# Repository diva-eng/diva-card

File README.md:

# Diva Card

Raspberry RP2040 based development board/card with builtin LED matrix

## Specs
* RP2040 Dual ARM Cortex-M0+ @ 133MHz
* Microchip ATECC608A crypto processor
* 8*5 WS2812C-2020 RGB LED matrix
* USB-C connector at USB 2.0 speed
* 1 user Button
* 1 user LED
* 13 user IO
* SWD tag connector
 * Edge connector for IO/Power

## Firmware

See the example firmware and build instructions in `fw/README.md`.

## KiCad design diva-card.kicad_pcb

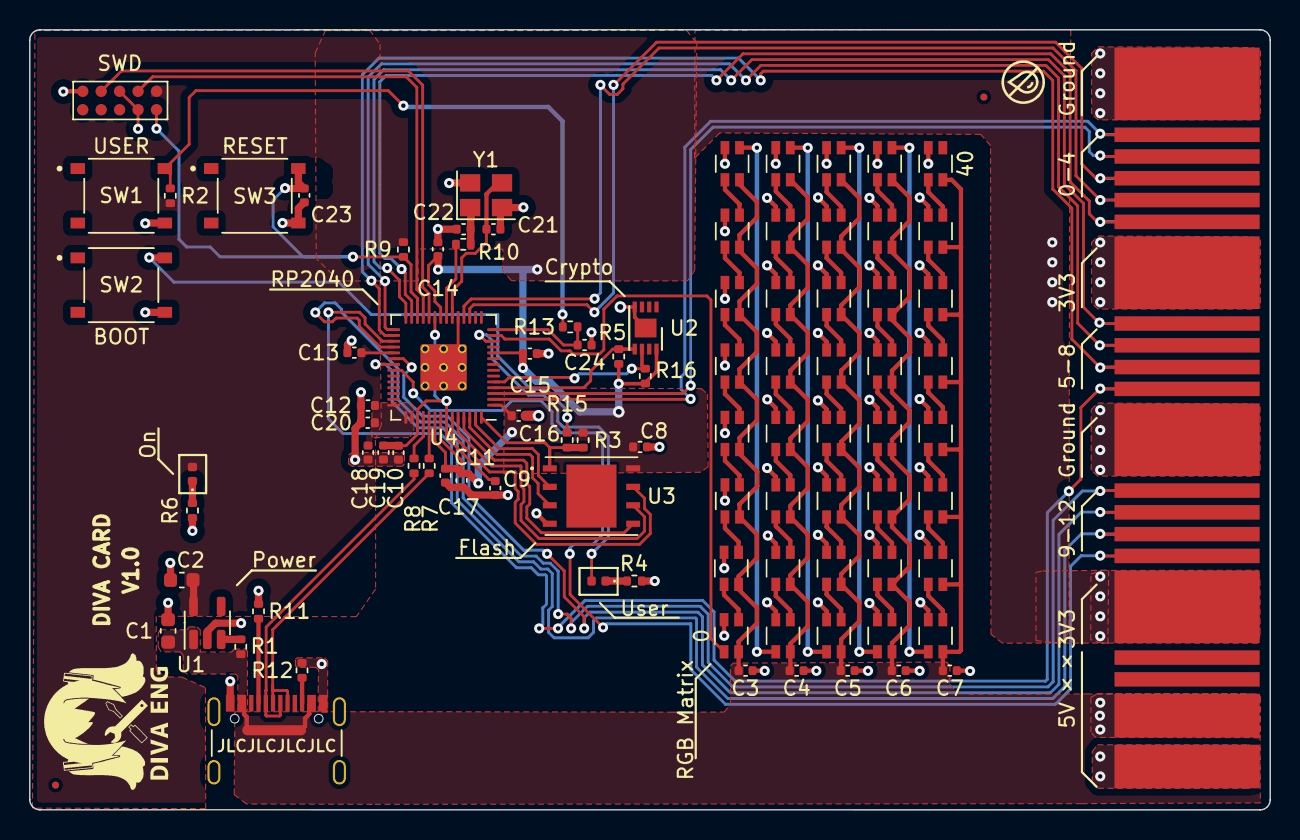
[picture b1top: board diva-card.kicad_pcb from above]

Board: 2 copper layers, 85.4 x 53.7 mm, 94 parts (0 on the bottom side), 84 nets.

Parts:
C1, C2: 10u; C_0603_1608Metric
C3, C4, C5, C6, C7, C8, C9, C10, C11, C12, C13, C14, C15, C16, C17, C18: 100n; C_0402_1005Metric
C19, C20, C23, C24: 1u; C_0402_1005Metric
C21, C22: 33p; C_0402_1005Metric
D1: EMERALD; LED_0402_1005Metric
D2: WHITE; LED_0402_1005Metric
FID1, FID2: Fiducial; Fiducial_0.5mm_Mask1mm
J1: Conn_02x05_Odd_Even; Tag-Connect_TC2050-IDC-NL_2x05_P1.27mm_Vertical
J2: USB_C_Receptacle_USB2.0; USB_C_Receptacle_Palconn_UTC16-G
J3: Conn_02x21_Odd_Even; PICO_CARD_EDGE_21
L1, L2, L3, L4, L5, L6, L7, L8, L9, L10, L11, L12, L13, L14, L15, L16, L17, L18, L19, L20, L21, L22, L23, L24, L25, L26, L27, L28, L29, L30, L31, L32, L33, L34, L35, L36, L37, L38, L39, L40: WS2812C; WS2812C-2020
R1, R2, R3, R13: 10k; R_0402_1005Metric
R4, R6: 1k5; R_0402_1005Metric
R5, R16: 4.7k; R_0402_1005Metric
R7, R8: 27; R_0402_1005Metric
R9: 10K; R_0402_1005Metric
R10: 100; R_0402_1005Metric
R11, R12: 5k1; R_0402_1005Metric
R15: 1K; R_0402_1005Metric
SW1: USER; SW_TS-1187A-B-A-B
SW2: BOOTSEL; SW_TS-1187A-B-A-B
SW3: RESET; SW_TS-1187A-B-A-B
U1: AP2112K-3.3; SOT-23-5
U2: ATECC608A-MAHDA; DFN-8-1EP_3x2mm_P0.5mm_EP1.3x1.5mm
U3: W25Q128XXX; W25Q128JVPIQ TR
U4: RP2040; RP2040-QFN-56
Y1: X322512MSB4SI; Crystal_SMD_3225-4Pin_3.2x2.5mm

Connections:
+1V1: C9.1, C10.1, C19.1, U4.23 (DVDD), U4.45 (VREG_VOUT), U4.50 (DVDD)
+3V3: C2.1, C8.1, C11.1, C12.1, C13.1, C14.1, C15.1, C16.1, C17.1, C18.1, C20.1, D2.2 (A), J1.1, J3.13, J3.14, J3.33, J3.34, R2.1, R3.1, R5.1, R9.1, R16.1, U1.5 (VOUT), U2.8 (VCC), U3.8 (VCC), U4.1 (IOVDD), U4.10 (IOVDD), U4.22 (IOVDD), U4.33 (IOVDD), U4.42 (IOVDD), U4.43 (ADC_AVDD), U4.44 (VREG_IN), U4.48 (USB_VDD), U4.49 (IOVDD)
+5V: C1.1, C3.1, C4.1, C5.1, C6.1, C7.1, J2.A4 (VBUS), J2.A9 (VBUS), J2.B4 (VBUS), J2.B9 (VBUS), J3.39, J3.40, L1.4 (VDD), L2.4 (VDD), L3.4 (VDD), L4.4 (VDD), L5.4 (VDD), L6.4 (VDD), L7.4 (VDD), L8.4 (VDD), L9.4 (VDD), L10.4 (VDD), L11.4 (VDD), L12.4 (VDD), L13.4 (VDD), L14.4 (VDD), L15.4 (VDD), L16.4 (VDD), L17.4 (VDD), L18.4 (VDD), L19.4 (VDD), L20.4 (VDD), L21.4 (VDD), L22.4 (VDD), L23.4 (VDD), L24.4 (VDD), L25.4 (VDD), L26.4 (VDD), L27.4 (VDD), L28.4 (VDD), L29.4 (VDD), L30.4 (VDD), L31.4 (VDD), L32.4 (VDD), L33.4 (VDD), L34.4 (VDD), L35.4 (VDD), L36.4 (VDD), L37.4 (VDD), L38.4 (VDD), L39.4 (VDD), L40.4 (VDD), R1.1, U1.1 (VIN)
/I2C0_SCL: R16.2, U2.6 (SCL), U4.5 (GPIO3)
/I2C0_SDA: R5.2, U2.5 (SDA), U4.4 (GPIO2)
/LED_DI: L1.3 (DI), U4.13 (GPIO10)
/USER_LED: D1.2 (A), U4.12 (GPIO9)
/connectors/SWDCLK: J1.4, U4.24 (SWCLK)
/connectors/SWDIO: J1.2, U4.25 (SWD)
/connectors/USB_D+: J2.A6 (D+), J2.B6 (D+), R7.2
/connectors/USB_D-: J2.A7 (D-), J2.B7 (D-), R8.2
/connectors/USER_IO_0: J3.3, J3.4, U4.2 (GPIO0)
/connectors/USER_IO_1: J3.5, J3.6, U4.3 (GPIO1)
/connectors/USER_IO_2: J3.7, J3.8, U4.17 (GPIO14)
/connectors/USER_IO_3: J3.9, J3.10, U4.18 (GPIO15)
/connectors/USER_IO_4: J3.11, J3.12, U4.27 (GPIO16)
/connectors/USER_IO_5: J3.15, J3.16, U4.28 (GPIO17)
/connectors/USER_IO_6: J3.17, J3.18, U4.29 (GPIO18)
/connectors/USER_IO_7: J3.19, J3.20, U4.30 (GPIO19)
/connectors/USER_IO_8: J3.21, J3.22, U4.31 (GPIO20)
/connectors/USER_IO_9: J3.25, J3.26, U4.32 (GPIO21)
/connectors/USER_IO_10: J3.27, J3.28, U4.34 (GPIO22)
/connectors/USER_IO_11: J3.29, J3.30, U4.35 (GPIO23)
/connectors/USER_IO_12: J3.31, J3.32, U4.36 (GPIO24)
/connectors/~RESET: C23.1, J1.10, R9.2, SW3.1, U4.26 (RUN)
/microcontroller/QSPI_SCLK: U3.6 (CLK), U4.52 (QSPI_SCLK)
/microcontroller/QSPI_SIO0: U3.5 (DI(IO0)), U4.53 (QSPI_SD0)
/microcontroller/QSPI_SIO1: U3.2 (DO(IO1)), U4.55 (QSPI_SD1)
/microcontroller/QSPI_SIO2: U3.3 (IO2), U4.54 (QSPI_SD2)
/microcontroller/QSPI_SIO3: U3.7 (IO3), U4.51 (QSPI_SD3)
/microcontroller/USB_DM: R8.1, U4.46 (USB_DM)
/microcontroller/USB_DP: R7.1, U4.47 (USB_DP)
/microcontroller/XIN: C21.2, U4.20 (XIN), Y1.3
/microcontroller/XOUT: R10.2, U4.21 (XOUT)
/microcontroller/~QSPI_CS: R3.2, R15.2, U3.1 (~CS), U4.56 (QSPI_SS)
/peripherals/~BOOT_SEL: R15.1, SW2.1
/~USER_SW0: C24.1, R13.1, U4.14 (GPIO11)
GND: C1.2, C2.2, C3.2, C4.2, C5.2, C6.2, C7.2, C8.2, C9.2, C10.2, C11.2, C12.2, C13.2, C14.2, C15.2, C16.2, C17.2, C18.2, C19.2, C20.2, C21.1, C22.1, C23.2, C24.2, J1.3, J1.5, J1.9, J2.A1 (GND), J2.A12 (GND), J2.B1 (GND), J2.B12 (GND), J2.S1 (SHIELD), J3.1, J3.2, J3.23, J3.24, J3.41, J3.42, L1.2 (GND), L2.2 (GND), L3.2 (GND), L4.2 (GND), L5.2 (GND), L6.2 (GND), L7.2 (GND), L8.2 (GND), L9.2 (GND), L10.2 (GND), L11.2 (GND), L12.2 (GND), L13.2 (GND), L14.2 (GND), L15.2 (GND), L16.2 (GND), L17.2 (GND), L18.2 (GND), L19.2 (GND), L20.2 (GND), L21.2 (GND), L22.2 (GND), L23.2 (GND), L24.2 (GND), L25.2 (GND), L26.2 (GND), L27.2 (GND), L28.2 (GND), L29.2 (GND), L30.2 (GND), L31.2 (GND), L32.2 (GND), L33.2 (GND), L34.2 (GND), L35.2 (GND), L36.2 (GND), L37.2 (GND), L38.2 (GND), L39.2 (GND), L40.2 (GND), R4.2, R6.2, R11.2, R12.2, SW1.2, SW2.2, SW3.2, U1.2 (GND), U2.4 (GND), U2.9 (EP), U3.4 (GND), U4.19 (TESTEN), U4.57 (GND), Y1.2, Y1.4
unnamed: C22.2, R10.1, Y1.1
unnamed: D1.1 (K), R4.1
unnamed: D2.1 (K), R6.1
unnamed: J2.A5 (CC1), R11.1
unnamed: J2.B5 (CC2), R12.1
unnamed: L1.1 (DO), L2.3 (DI)
unnamed: L2.1 (DO), L3.3 (DI)
unnamed: L3.1 (DO), L4.3 (DI)
unnamed: L4.1 (DO), L5.3 (DI)
unnamed: L5.1 (DO), L6.3 (DI)
unnamed: L6.1 (DO), L7.3 (DI)
unnamed: L7.1 (DO), L8.3 (DI)
unnamed: L8.1 (DO), L9.3 (DI)
unnamed: L10.1 (DO), L11.3 (DI)
unnamed: L9.1 (DO), L10.3 (DI)
unnamed: L11.1 (DO), L12.3 (DI)
unnamed: L12.1 (DO), L13.3 (DI)
unnamed: L13.1 (DO), L14.3 (DI)
unnamed: L14.1 (DO), L15.3 (DI)
unnamed: L15.1 (DO), L16.3 (DI)
unnamed: L16.1 (DO), L17.3 (DI)
unnamed: L17.1 (DO), L18.3 (DI)
unnamed: L18.1 (DO), L19.3 (DI)
unnamed: L19.1 (DO), L20.3 (DI)
unnamed: L20.1 (DO), L21.3 (DI)
unnamed: L21.1 (DO), L22.3 (DI)
unnamed: L22.1 (DO), L23.3 (DI)
unnamed: L23.1 (DO), L24.3 (DI)
unnamed: L24.1 (DO), L25.3 (DI)
unnamed: L25.1 (DO), L26.3 (DI)
unnamed: L26.1 (DO), L27.3 (DI)
unnamed: L27.1 (DO), L28.3 (DI)
unnamed: L28.1 (DO), L29.3 (DI)
unnamed: L29.1 (DO), L30.3 (DI)
unnamed: L30.1 (DO), L31.3 (DI)
unnamed: L31.1 (DO), L32.3 (DI)
unnamed: L32.1 (DO), L33.3 (DI)
unnamed: L33.1 (DO), L34.3 (DI)
unnamed: L34.1 (DO), L35.3 (DI)
unnamed: L35.1 (DO), L36.3 (DI)
unnamed: L36.1 (DO), L37.3 (DI)
unnamed: L37.1 (DO), L38.3 (DI)
unnamed: L38.1 (DO), L39.3 (DI)
unnamed: L39.1 (DO), L40.3 (DI)
unnamed: R1.2, U1.3 (EN)
unnamed: R2.2, R13.2, SW1.1

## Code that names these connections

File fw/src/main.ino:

#include <Arduino.h>
#include <Wire.h>

// Pin mapping from the schematic:
// USER_LED => GPIO9
// LED DI (WS2812 data) => GPIO10
// I2C0_SDA => GPIO2, I2C0_SCL => GPIO3 (Wire.begin() uses default SDA/SCL)

const int USER_LED_PIN = 9;
const int LED_DATA_PIN = 10;

// CryptoAuthLib (Microchip) headers
#include <cryptoauthlib.h>

void printHex(const uint8_t* data, size_t len) {
  for (size_t i = 0; i < len; ++i) {
    if (data[i] < 0x10) Serial.print('0');
    Serial.print(data[i], HEX);
    if (i + 1 < len) Serial.print(':');
  }
}

void setup() {
  Serial.begin(115200);
  while (!Serial) {
    delay(10);
  }
  Serial.println("Diva Card example firmware (Arduino RP2040)");

  // Initialize user LED pin
  pinMode(USER_LED_PIN, OUTPUT);
  digitalWrite(USER_LED_PIN, LOW);

  // Initialize LED data pin (for external WS2812 chain if used)
  pinMode(LED_DATA_PIN, OUTPUT);
  digitalWrite(LED_DATA_PIN, LOW);

  // Initialize I2C bus (Wire uses default SDA/SCL pins mapped in board)
  Wire.begin();
  Serial.println("I2C initialized (Wire.begin)");

  // Initialize CryptoAuthLib to talk to ATECC608A over I2C
  ATCA_STATUS status = ATCA_GEN_FAIL;
  Serial.print("Initializing CryptoAuthLib... ");
  // Use the default I2C interface cfg built into the library (cfg_ateccx08a_i2c_default)
  status = atcab_init(&cfg_ateccx08a_i2c_default);
  if (status != ATCA_SUCCESS) {
    Serial.print("failed (status=0x"); Serial.print(status, HEX); Serial.println(")");
  } else {
    Serial.println("ok");

    // Wake the device (library provides helper)
    status = atcab_wakeup(NULL);
    if (status != ATCA_SUCCESS) {
      Serial.print("ATECC wake failed (0x"); Serial.print(status, HEX); Serial.println(")");
    } else {
      Serial.println("ATECC woke up");

      // Read the 9-byte serial number
      uint8_t serial_num[9] = {0};
      status = atcab_read_serial_number(serial_num);
      if (status == ATCA_SUCCESS) {
        Serial.print("ATECC serial: ");
        printHex(serial_num, sizeof(serial_num));
        Serial.println();
      } else {
        Serial.print("Failed to read serial (0x"); Serial.print(status, HEX); Serial.println(")");
      }

      // Put the device back to sleep
      atcab_sleep();
    }
  }
}

unsigned long lastToggle = 0;
bool ledState = false;

void loop() {
  unsigned long now = millis();
  if (now - lastToggle > 500) {
    ledState = !ledState;
    digitalWrite(USER_LED_PIN, ledState ? HIGH : LOW);
    lastToggle = now;
  }
}

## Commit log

2022-05-31 Init commit, schematic design, footprints
2022-05-31 adding readme
2022-06-01 All component except led matrix
2022-06-01 finish schematic, prep pcb
2022-06-05 Basic routing MCU, crystal, flash, crypto
2022-06-07 Basic routing complete, rename
2022-06-07 Adding test gerber and bom
2022-06-08 updating footprints to udfn
2022-06-11 Adding schematic pdf
2022-06-12 schematic update
2022-06-13 design flaw fix
2022-06-13 update schematic and photo
2022-06-13 Remove trace under usb trace
2022-06-13 Update render
2022-06-15 update power delivery
2022-06-15 update schematic
2022-06-23 Production Design V1.0
2022-07-07 Fix issues found on production prototype
2022-07-07 adding board config
2025-12-08 adding firmware
